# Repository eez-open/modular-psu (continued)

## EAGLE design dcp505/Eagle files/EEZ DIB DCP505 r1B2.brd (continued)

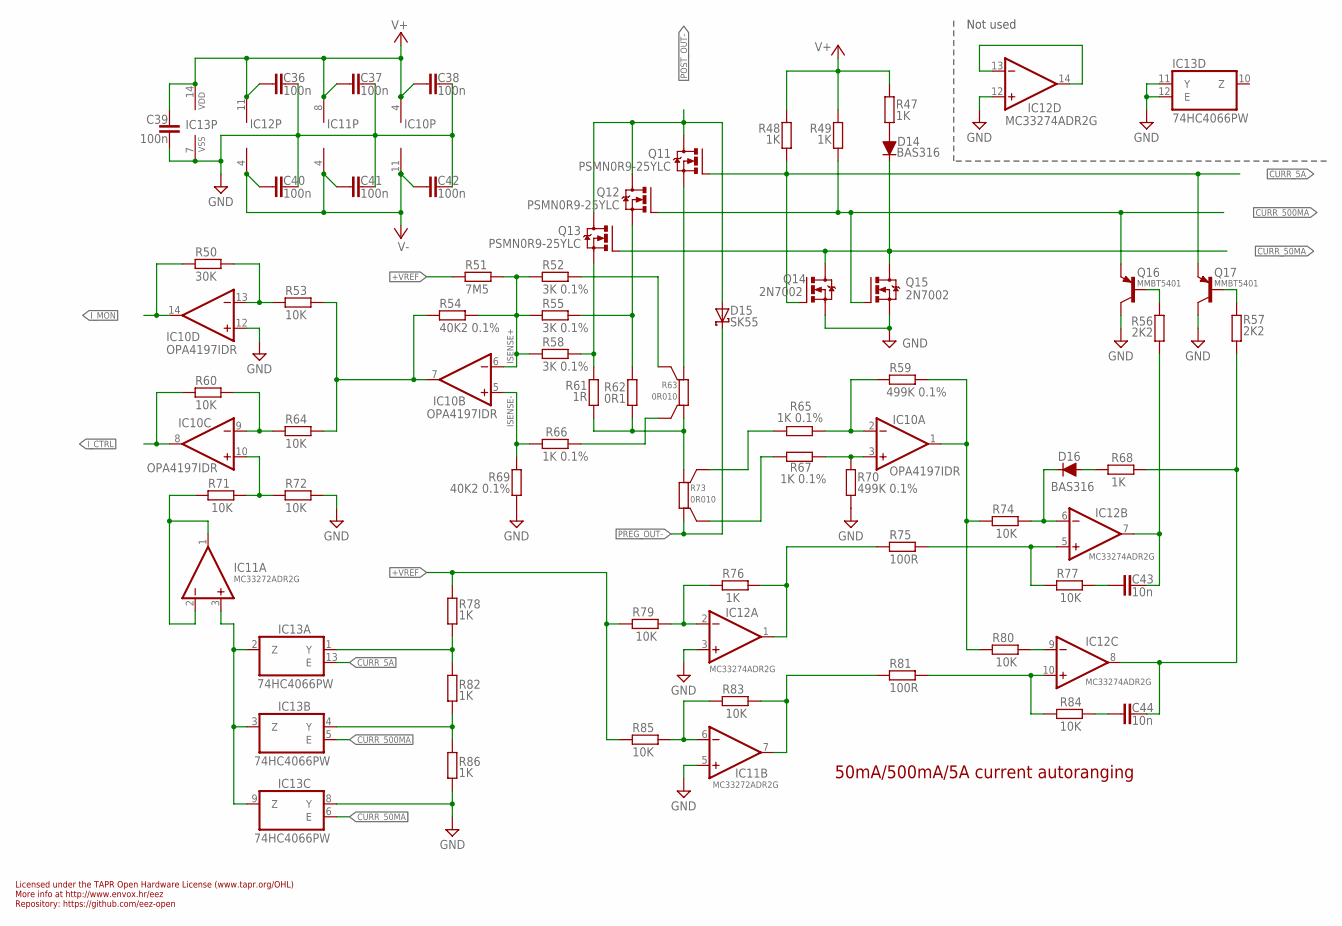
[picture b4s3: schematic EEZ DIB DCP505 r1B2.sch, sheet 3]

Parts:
C36, C37, C38, C39, C40, C41, C42: 100n; C0603
C43, C44: 10n; C0603
D14, D16: BAS316; SOD323-R
D15: SK55; SMB
IC10: OPA4197IDR; SOIC127P600X175-14N
IC11: MC33272ADR2G; SOIC127P600X173-8N
IC12: MC33274ADR2G; SOIC127P600X175-14N
IC13: 74HC4066PW; SOP65P640X120-14N
Q11, Q12, Q13: PSMN0R9-25YLC; SOT669
Q14, Q15: 2N7002; SOT103P240X110-3N; MPN 2N7002-7-F
Q16, Q17: MMBT5401; SOT23-BEC
R47, R48, R49, R68, R76, R78, R82, R86: 1K; R0805
R50: 30K; R0805
R51: 7M5; R0805
R52, R55, R58: 3K 0.1%; R0603
R53, R60, R64, R71, R72, R74, R77, R79, R80, R83, R84, R85: 10K; R0805
R54, R69: 40K2 0.1%; R0603
R56, R57: 2K2; R0805
R59, R70: 499K 0.1%; R0603
R61: 1R; R0805
R62: 0R1; R1206
R63, R73: 0R010; R_H2728
R65, R66, R67: 1K 0.1%; R0603
R75, R81: 100R; R0805

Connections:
+VREF: R51.1, R78.2, R79.2, R85.2; also elsewhere on the board
CURR_5A: IC13.13 (E), Q11.4 (G), Q14.1 (G), Q17.E, R48.2; also elsewhere on the board
CURR_50MA: D14.C, IC13.6 (E), Q13.4 (G), Q14.3 (D), Q15.3 (D); also elsewhere on the board
CURR_500MA: IC13.5 (E), Q12.4 (G), Q15.1 (G), Q16.E, R49.2; also elsewhere on the board
GND: C36.2, C37.2, C38.2, C39.1, C40.2, C41.2, C42.2, IC10.12 (+IN), IC11.5 (+IN), IC12.3 (+IN), IC12.12 (+IN), IC13.7 (VSS), IC13.8 (Y), IC13.11 (Y), IC13.12 (E), Q14.2 (S), Q15.2 (S), Q16.C, Q17.C, R69.1, R70.2, R72.1, R86.1; also elsewhere on the board
ISENSE+: IC10.6 (-IN), R51.2, R52.2, R54.1, R55.2, R58.2
ISENSE-: IC10.5 (+IN), R66.2, R69.2
I_CTRL: IC10.8 (OUT), R60.2; also elsewhere on the board
I_MON: IC10.14 (OUT), R50.2; also elsewhere on the board
unnamed: R65.2, R73.2S
unnamed: R61.2, R62.1, R63.1, R73.2
unnamed: IC11.1 (OUT), IC11.2 (-IN), R71.2
unnamed: IC11.6 (-IN), R83.2, R85.1
unnamed: IC10.2 (-IN), R59.2, R65.1
unnamed: Q11.1 (S), Q11.2 (S), Q11.3 (S), R63.2
unnamed: D14.A, R47.2
unnamed: IC10.1 (OUT), R59.1, R74.2, R80.2
unnamed: IC11.3 (+IN), IC13.2 (Z), IC13.3 (Z), IC13.9 (Z)
unnamed: C43.2, IC12.7 (OUT), R56.2
unnamed: Q16.B, R56.1
unnamed: Q17.B, R57.1
unnamed: IC10.7 (OUT), R53.1, R54.2, R64.1
unnamed: IC10.9 (-IN), R60.1, R64.2
unnamed: IC13.1 (Y), R78.1, R82.2
unnamed: C44.2, IC12.8 (OUT), R57.2, R68.2
unnamed: IC10.10 (+IN), R71.1, R72.2
unnamed: IC13.4 (Y), R82.1, R86.2
unnamed: IC11.7 (OUT), R81.2, R83.1
unnamed: IC10.13 (-IN), R50.1, R53.2
unnamed: R67.2, R73.1S
unnamed: R63.1S, R66.1
unnamed: IC12.2 (-IN), R76.2, R79.1
unnamed: IC12.1 (OUT), R75.2, R76.1
unnamed: IC10.3 (+IN), R67.1, R70.1
unnamed: IC12.13 (-IN), IC12.14 (OUT)
unnamed: Q12.1 (S), Q12.2 (S), Q12.3 (S), R55.1, R62.2
unnamed: D16.C, IC12.6 (-IN), R74.1
unnamed: IC12.5 (+IN), R75.1, R77.2
unnamed: R52.1, R63.2S
unnamed: IC12.9 (-IN), R80.1
unnamed: IC12.10 (+IN), R81.1, R84.2
unnamed: Q13.1 (S), Q13.2 (S), Q13.3 (S), R58.1, R61.1
unnamed: C43.1, R77.1
unnamed: C44.1, R84.1
unnamed: D16.A, R68.1
POST_OUT-: D15.A, Q11.MB (D), Q12.MB (D), Q13.MB (D); also elsewhere on the board
PREG_OUT-: D15.C, R73.1; also elsewhere on the board
V+: C36.1, C37.1, C38.1, C39.2, IC10.4 (V+), IC11.8 (V+), IC12.11 (V-), IC13.14 (VDD), R47.1, R48.1, R49.1; also elsewhere on the board
V-: C40.1, C41.1, C42.1, IC10.11 (V-), IC11.4 (V-), IC12.4 (V+); also elsewhere on the board

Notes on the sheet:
Licensed under the TAPR Open Hardware License (www.tapr.org/OHL)
Repository: https://github.com/eez-open
More info at http://www.envox.hr/eez
50mA/500mA/5A current autoranging
Not used

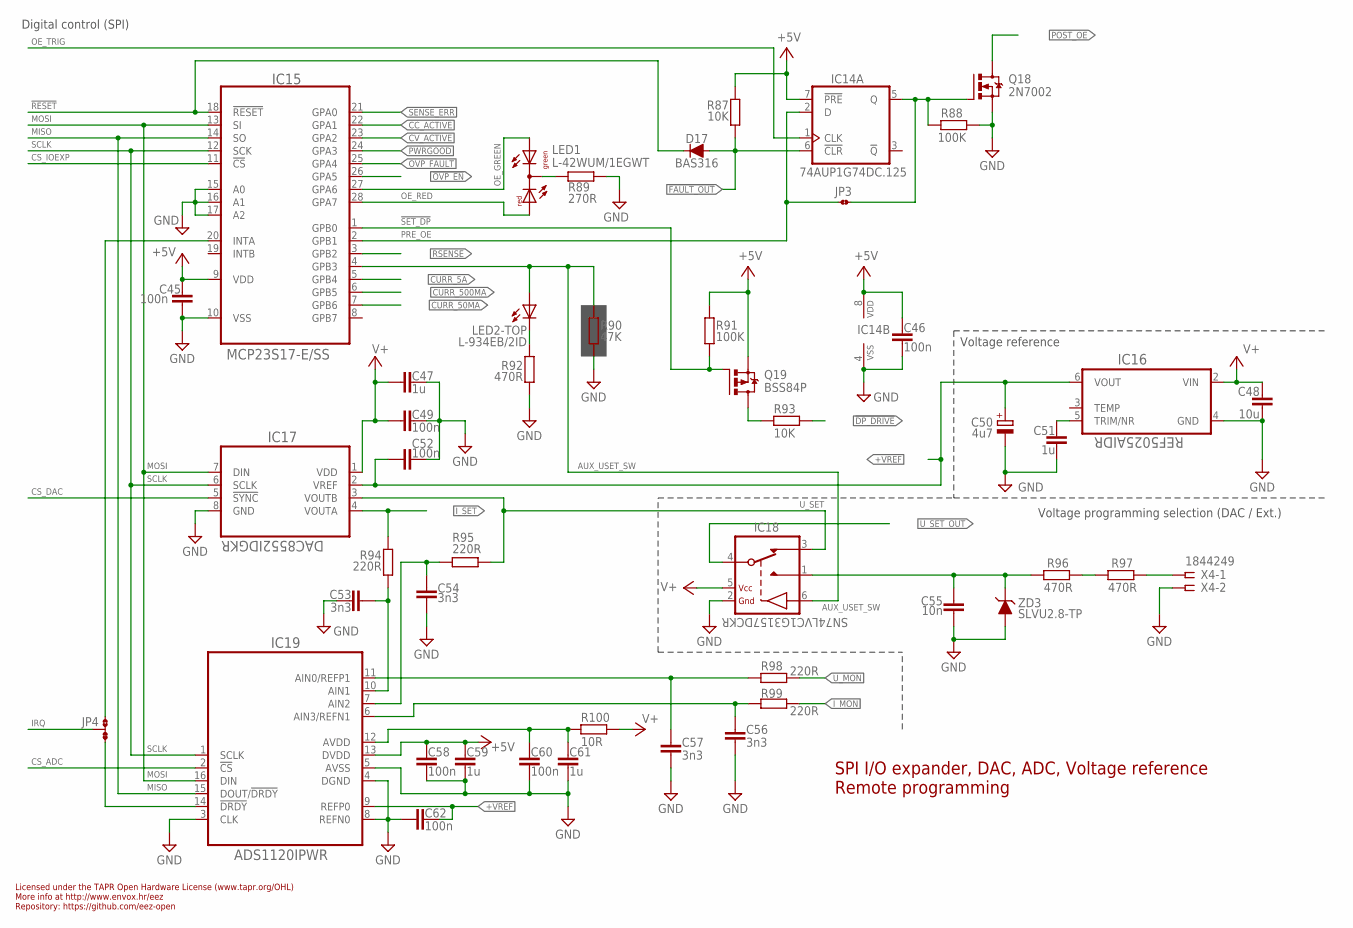
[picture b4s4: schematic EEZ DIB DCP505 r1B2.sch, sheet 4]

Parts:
C45, C46, C49, C52, C58, C60, C62: 100n; C0603
C47, C51, C59, C61: 1u; C0805
C48: 10u; C1206
C50: 4u7; EC1206
C53, C54, C56, C57: 3n3; C0805
C55: 10n; C0805
D17: BAS316; SOD323-R
IC14: 74AUP1G74DC.125; DCU8
IC15: MCP23S17-E/SS; SOP65P780X200-28N
IC16: REF5025AIDR; SOIC127P600X175-8N
IC17: DAC8552IDGKR; DGK8-M
IC18: SN74LVC1G3157DCKR; SOT65P210X110-6N
IC19: ADS1120IPWR; PW(R-PDSO-G16)
JP3: JP2-CUT
JP4: JP3-CUT
LED1: L-42WUM/1EGWT; L-42WUM-1EGWT
LED2: L-934EB/2ID; L-934EB
Q18: 2N7002; SOT103P240X110-3N; MPN 2N7002-7-F
Q19: BSS84P; SOT95P237X112-3N
R87, R93: 10K; R0805
R88, R91: 100K; R0805
R89: 270R; R0805
R90: 47K; R0805
R92, R96, R97: 470R; R0805
R94, R95, R98, R99: 220R; R0805
R100: 10R; R0805
X4: 1844249; MC1,5/5-G-3,5
ZD3: SLVU2.8-TP; SOT23

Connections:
!DP_DRIVE: R93.1; also elsewhere on the board
!DRDY: IC19.14 (!DRDY), JP4.NC
!FAULT_OUT: D17.A, IC14.6 (!CLR), R87.2; also elsewhere on the board
!OVP_EN: IC15.26 (GPA5); also elsewhere on the board
!RESET: D17.C, IC15.18 (!RESET); also elsewhere on the board
!SET_DP: IC15.1 (GPB0), Q19.1 (G), R91.2
+5V: C45.1, C46.2, C58.2, C59.2, IC14.7 (!PRE), IC14.8 (VDD), IC15.9 (VDD), IC19.13 (DVDD), Q19.2 (S), R87.1, R91.1; also elsewhere on the board
+VREF: C50.+, C52.2, C62.2, IC16.6 (VOUT), IC17.2 (VREF), IC19.9 (REFP0); also elsewhere on the board
AUX_IN: C55.2, IC18.1 (NO), R96.1, ZD3.3 (C)
AUX_USET_SW: IC15.4 (GPB3), IC18.6 (CTRL), LED2.TA (A), R90.2
CC_ACTIVE: IC15.22 (GPA1); also elsewhere on the board
CS_ADC: IC19.2 (!CS); also elsewhere on the board
CS_DAC: IC17.5 (!SYNC); also elsewhere on the board
CS_IOEXP: IC15.11 (!CS); also elsewhere on the board
CURR_5A: IC15.5 (GPB4); also elsewhere on the board
CURR_50MA: IC15.7 (GPB6); also elsewhere on the board
CURR_500MA: IC15.6 (GPB5); also elsewhere on the board
CV_ACTIVE: IC15.23 (GPA2); also elsewhere on the board
DP_LED: Q19.3 (D), R93.2
GND: C45.2, C46.1, C47.2, C48.2, C49.1, C50.-, C51.2, C52.1, C53.1, C54.1, C55.1, C56.2, C57.1, C58.1, C59.1, C60.1, C61.1, C62.1, IC14.4 (VSS), IC15.10 (VSS), IC15.15 (A0), IC15.16 (A1), IC15.17 (A2), IC16.4 (GND), IC17.8 (GND), IC18.2 (GND), IC19.3 (CLK), IC19.4 (DGND), IC19.5 (AVSS), IC19.8 (REFN0), Q18.2 (S), R88.1, R89.2, R90.1, R92.1, X4.2, ZD3.1 (A), ZD3.2 (A); also elsewhere on the board
IRQ: JP4.COM; also elsewhere on the board
I_MON: R99.1; also elsewhere on the board
I_SET: IC17.4 (VOUTA), R94.1; also elsewhere on the board
MISO: IC15.14 (SO), IC19.15 (DOUT/!DRDY); also elsewhere on the board
MOSI: IC15.13 (SI), IC17.7 (DIN), IC19.16 (DIN); also elsewhere on the board
unnamed: IC15.20 (INTA), JP4.NO
unnamed: LED1.CC (C), R89.1
unnamed: R96.2, R97.1
unnamed: R97.2, X4.1
unnamed: IC14.5 (Q), JP3.2, Q18.1 (G), R88.2
unnamed: C60.2, C61.2, IC19.12 (AVDD), R100.2
unnamed: C51.1, IC16.5 (TRIM/NR)
unnamed: C53.2, IC19.10 (AIN1), R94.2
unnamed: C57.2, IC19.11 (AIN0/REFP1), R98.2
unnamed: C54.2, IC19.7 (AIN2), R95.2
unnamed: C56.1, IC19.6 (AIN3/REFN1), R99.2
unnamed: LED2.TC (C), R92.2
OE_GREEN: IC15.27 (GPA6), LED1.GREEN (AG)
OE_RED: IC15.28 (GPA7), LED1.RED (AR)
OE_TRIG: IC14.1 (CLK); also elsewhere on the board
OVP_FAULT: IC15.25 (GPA4); also elsewhere on the board
POST_OE: Q18.3 (D); also elsewhere on the board
PRE_OE: IC14.2 (D), IC15.2 (GPB1), JP3.1
PWRGOOD: IC15.24 (GPA3); also elsewhere on the board
RSENSE: IC15.3 (GPB2); also elsewhere on the board
SCLK: IC15.12 (SCK), IC17.6 (SCLK), IC19.1 (SCLK); also elsewhere on the board
SENSE_ERR: IC15.21 (GPA0); also elsewhere on the board
U_MON: R98.1; also elsewhere on the board
U_SET: IC17.3 (VOUTB), IC18.3 (NC), R95.1; also elsewhere on the board
U_SET_OUT: IC18.4 (COM); also elsewhere on the board
V+: C47.1, C48.1, C49.2, IC16.2 (VIN), IC17.1 (VDD), IC18.5 (VDD), R100.1; also elsewhere on the board

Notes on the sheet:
SPI I/O expander, DAC, ADC, Voltage reference
Digital control (SPI)
Voltage reference
Licensed under the TAPR Open Hardware License (www.tapr.org/OHL)
Repository: https://github.com/eez-open
More info at http://www.envox.hr/eez
Remote programming
Voltage programming selection (DAC / Ext.)

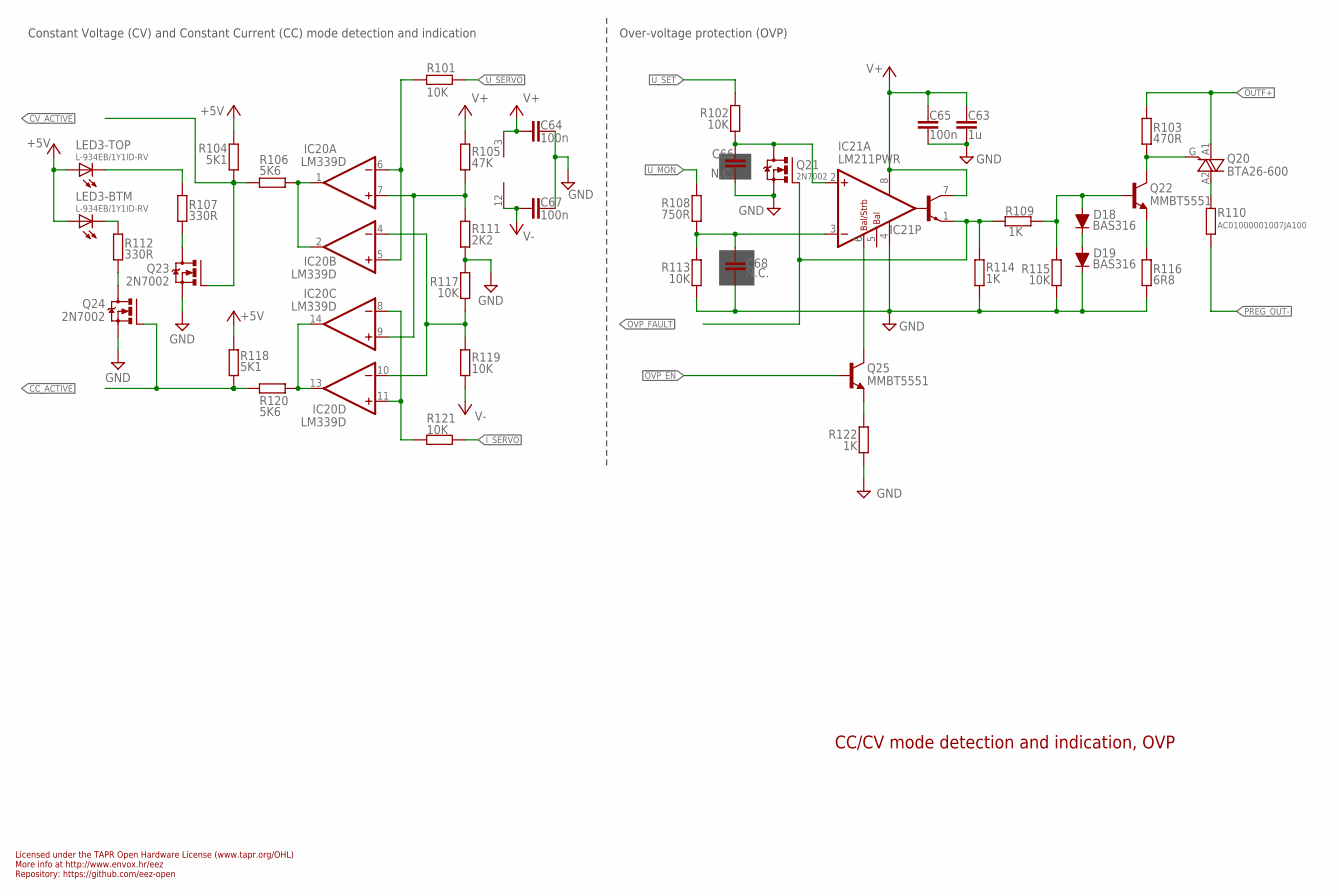
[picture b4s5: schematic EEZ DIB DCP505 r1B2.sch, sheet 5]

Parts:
C63: 1u; C0805
C64, C65, C67: 100n; C0603
C66, C68: N.C.; C0805
D18, D19: BAS316; SOD323-R
IC20: LM339D; SOIC127P600X175-14N
IC21: LM211PWR; PW8_TSSOP8
LED3: L-934EB/1Y1ID-RV; L-934EB
Q20: BTA26-600; TOP3_TRIAC_NOHOLE
Q21: 2N7002; SOT103P240X110-3N; MPN 2N7002-7-F
Q22, Q25: MMBT5551; SOT23-BEC
Q23, Q24: 2N7002; SOT103P240X110-3N
R101, R102, R113, R115, R117, R119, R121: 10K; R0805
R103: 470R; R0805
R104, R118: 5K1; R0805
R105: 47K; R0805
R106, R120: 5K6; R0805
R107, R112: 330R; R0805
R108: 750R; R0805
R109, R114, R122: 1K; R0805
R110: AC01000001007JA100; 0411/15
R111: 2K2; R0805
R116: 6R8; R0805

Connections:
!OVP_EN: Q25.B; also elsewhere on the board
+5V: LED3.BA (A), LED3.TA (A), R104.2, R118.2; also elsewhere on the board
CC_ACTIVE: Q24.1 (G), R118.1, R120.2; also elsewhere on the board
CC_LED: LED3.BC (C), R112.2
CV_ACTIVE: Q23.1 (G), R104.1, R106.2; also elsewhere on the board
CV_LED: LED3.TC (C), R107.1
GND: C63.2, C64.1, C65.1, C66.1, C67.1, C68.1, D19.C, IC21.4 (V-), Q21.2 (S), Q23.2 (S), Q24.2 (S), R111.1, R113.2, R114.2, R115.1, R116.1, R117.2, R122.2; also elsewhere on the board
I_SERVO: R121.1; also elsewhere on the board
unnamed: Q20.A2, R110.2
unnamed: Q20.G, Q22.C, R103.1
unnamed: Q22.E, R116.2
unnamed: D18.C, D19.A
unnamed: D18.A, Q22.B, R109.1, R115.2
unnamed: IC21.6 (BAL/STRB), Q25.C
unnamed: Q25.E, R122.1
unnamed: C66.2, IC21.2 (+IN), Q21.3 (D), R102.2
unnamed: C68.2, IC21.3 (-IN), R108.2, R113.1
unnamed: Q24.3 (D), R112.1
unnamed: IC20.1 (OUT), IC20.2 (OUT), R106.1
unnamed: IC20.13 (OUT), IC20.14 (OUT), R120.1
unnamed: Q23.3 (D), R107.2
unnamed: IC20.5 (+IN), IC20.6 (-IN), R101.2
unnamed: IC20.8 (-IN), IC20.11 (+IN), R121.2
unnamed: IC20.7 (+IN), IC20.9 (+IN), R105.1, R111.2
unnamed: IC20.4 (-IN), IC20.10 (-IN), R117.1, R119.2
OUTF+: Q20.A1, R103.2; also elsewhere on the board
OVP_FAULT: IC21.1 (E), Q21.1 (G), R109.2, R114.1; also elsewhere on the board
PREG_OUT-: R110.1; also elsewhere on the board
U_MON: R108.1; also elsewhere on the board
U_SERVO: R101.1; also elsewhere on the board
U_SET: R102.1; also elsewhere on the board
V+: C63.1, C64.2, C65.2, IC20.3 (V+), IC21.7 (C), IC21.8 (V+), R105.2; also elsewhere on the board
V-: C67.2, IC20.12 (GND), R119.1; also elsewhere on the board

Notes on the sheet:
Licensed under the TAPR Open Hardware License (www.tapr.org/OHL)
Repository: https://github.com/eez-open
More info at http://www.envox.hr/eez
CC/CV mode detection and indication, OVP
Constant Voltage (CV) and Constant Current (CC) mode detection and indication
Over-voltage protection (OVP)

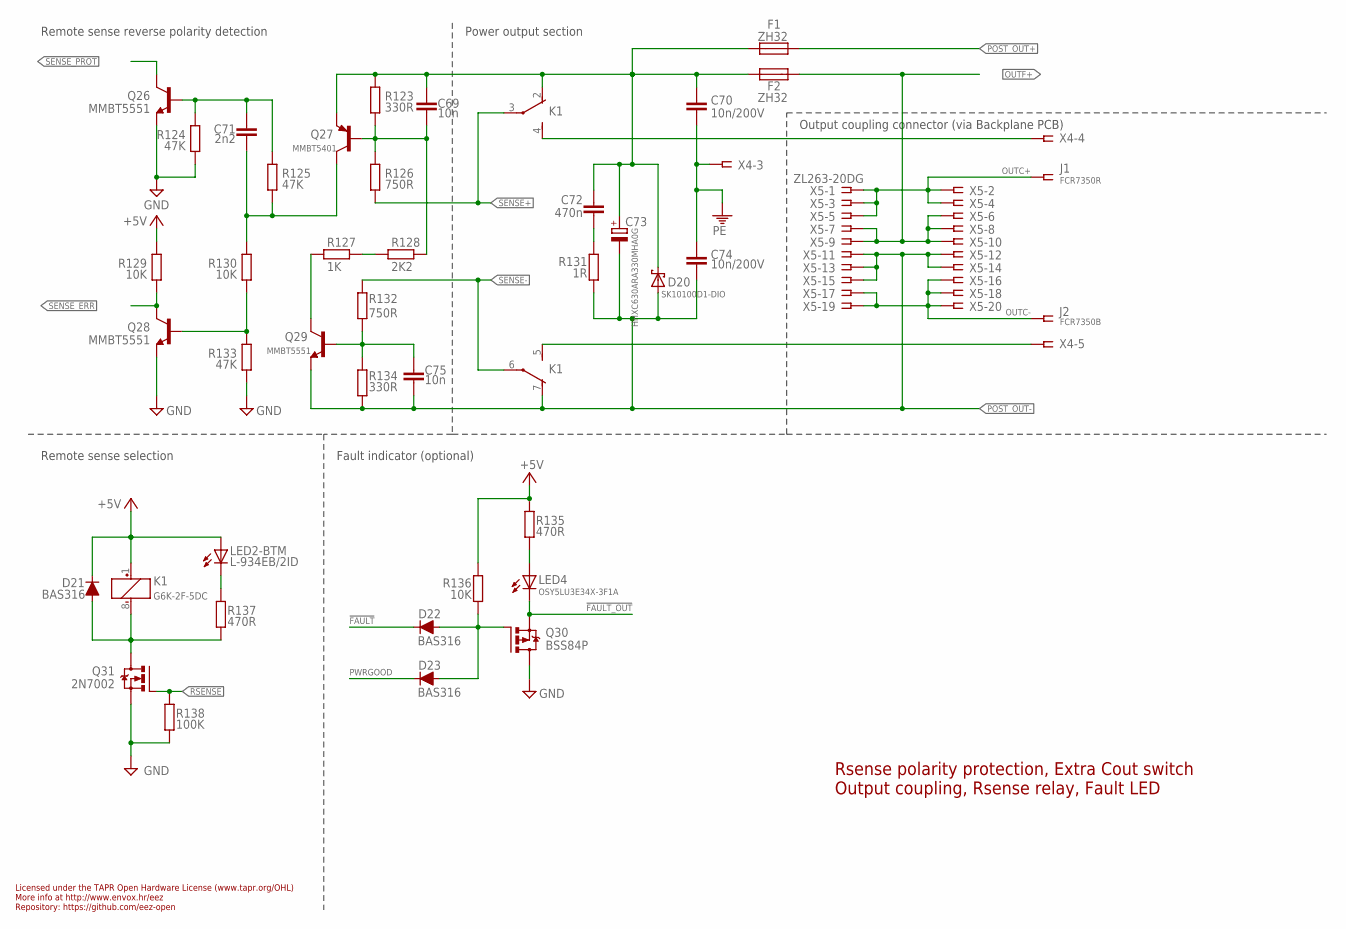
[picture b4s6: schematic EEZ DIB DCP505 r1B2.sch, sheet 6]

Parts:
C69, C75: 10n; C0805
C70, C74: 10n/200V; C1206
C71: 2n2; C0805
C72: 470n; C1206
C73: HHXC630ARA330MHA0G; CAPAE830X1050N
D20: SK10100D1-DIO; TO252-L
D21, D22, D23: BAS316; SOD323-R
F1, F2: ZH32
J1: FCR7350R; S16N-PC
J2: FCR7350B; S16N-PC
K1: G6K-2F-5DC; G6K-2F; MPN G6K-2F DC24
LED2: L-934EB/2ID; L-934EB
LED4: OSY5LU3E34X-3F1A; OSG8
Q26, Q28, Q29: MMBT5551; SOT23-BEC
Q27: MMBT5401; SOT23-BEC
Q30: BSS84P; SOT95P237X112-3N
Q31: 2N7002; SOT103P240X110-3N; MPN 2N7002-7-F
R123, R134: 330R; R0805
R124, R125, R133: 47K; R0805
R126, R132: 750R; R0805
R127: 1K; R0805
R128: 2K2; R0805
R129, R130, R136: 10K; R0805
R131: 1R; R0805
R135, R137: 470R; R0805
R138: 100K; R0805
X4: 1844249; MC1,5/5-G-3,5
X5: ZL263-20DG; SSW-110-02-T-D-RA

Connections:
!FAULT: D22.C; also elsewhere on the board
!FAULT_OUT: LED4.C, Q30.2 (S); also elsewhere on the board
+5V: D21.C, K1.1 (+), LED2.BA (A), R129.2, R135.2, R136.1; also elsewhere on the board
GND: Q26.E, Q28.E, Q30.3 (D), Q31.2 (S), R124.1, R133.1, R138.1; also elsewhere on the board
unnamed: C69.1, C70.1, C72.1, C73.+, D20.3 (C), F1.2, F2.1, K1.2 (O), Q27.E, R123.2
unnamed: D22.A, D23.A, Q30.1 (G), R136.2
unnamed: LED4.A, R135.1
unnamed: C69.2, Q27.B, R123.1, R126.2, R128.2
unnamed: C71.2, Q27.C, R125.1, R130.2
unnamed: Q29.C, R127.1
unnamed: C75.1, Q29.B, R132.1, R134.2
unnamed: C71.1, Q26.B, R124.2, R125.2
unnamed: Q28.B, R130.1, R133.2
unnamed: C72.2, R131.2
unnamed: D21.A, K1.8 (-), Q31.3 (D), R137.1
unnamed: K1.4 (S), X4.4
unnamed: K1.5 (S), X4.5
unnamed: LED2.BC (C), R137.2
unnamed: R127.2, R128.1
OUTC+: J1.1, J1.NC1, J1.NC2, J1.NC3, J1.NC4, X5.1, X5.2, X5.3, X5.4, X5.5
OUTC-: J2.1, J2.NC1, J2.NC2, J2.NC3, J2.NC4, X5.16, X5.17, X5.18, X5.19, X5.20
OUTF+: F2.2, X5.6, X5.7, X5.8, X5.9, X5.10; also elsewhere on the board
PE: C70.2, C74.1, X4.3; also elsewhere on the board
POST_OUT+: F1.1; also elsewhere on the board
POST_OUT-: C73.-, C74.2, C75.2, D20.1 (A), D20.2 (A), K1.7 (O), Q29.E, R131.1, R134.1, X5.11, X5.12, X5.13, X5.14, X5.15; also elsewhere on the board
PWRGOOD: D23.C; also elsewhere on the board
RSENSE: Q31.1 (G), R138.2; also elsewhere on the board
SENSE+: K1.3, R126.1; also elsewhere on the board
SENSE-: K1.6, R132.2; also elsewhere on the board
SENSE_ERR: Q28.C, R129.1; also elsewhere on the board
SENSE_PROT: Q26.C; also elsewhere on the board

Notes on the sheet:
Rsense polarity protection, Extra Cout switch
Licensed under the TAPR Open Hardware License (www.tapr.org/OHL)
Repository: https://github.com/eez-open
More info at http://www.envox.hr/eez
Remote sense reverse polarity detection
Remote sense selection
Output coupling, Rsense relay, Fault LED
Fault indicator (optional)
Output coupling connector (via Backplane PCB)
Power output section

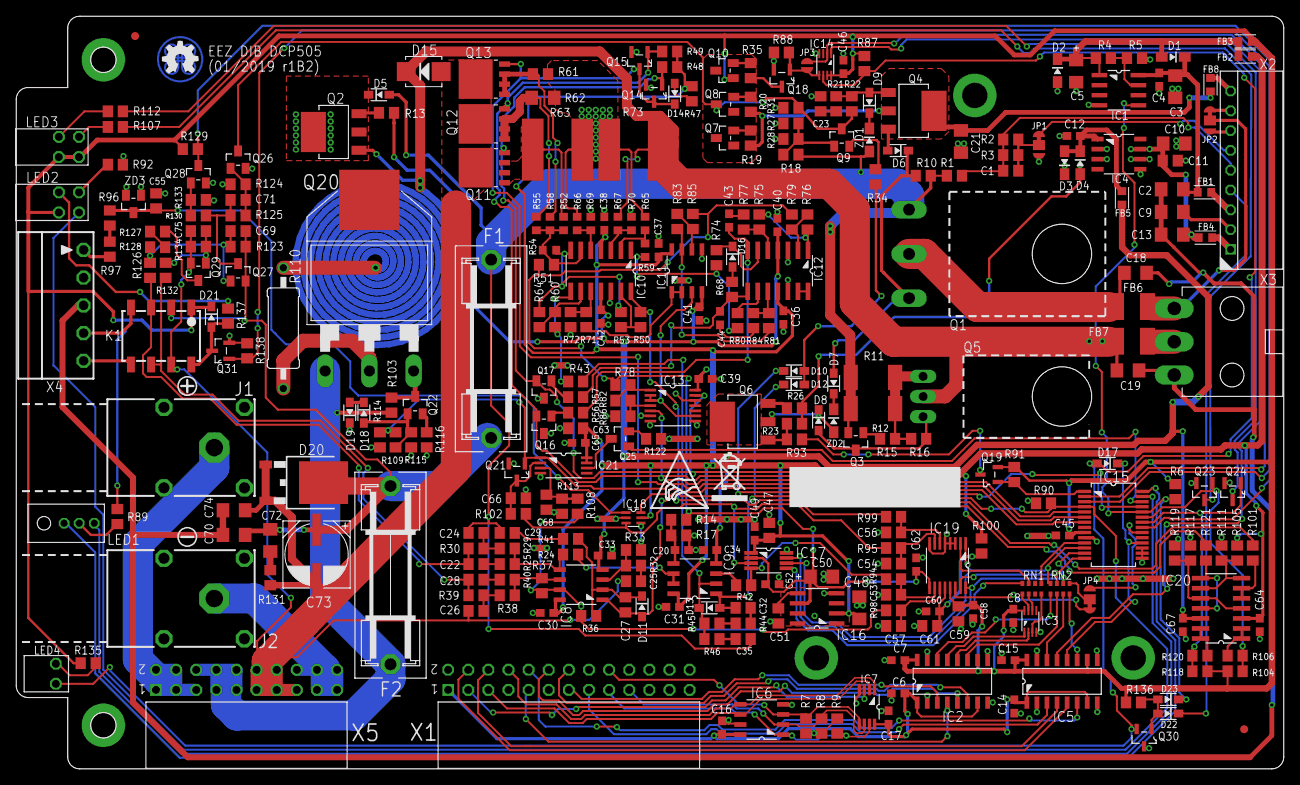
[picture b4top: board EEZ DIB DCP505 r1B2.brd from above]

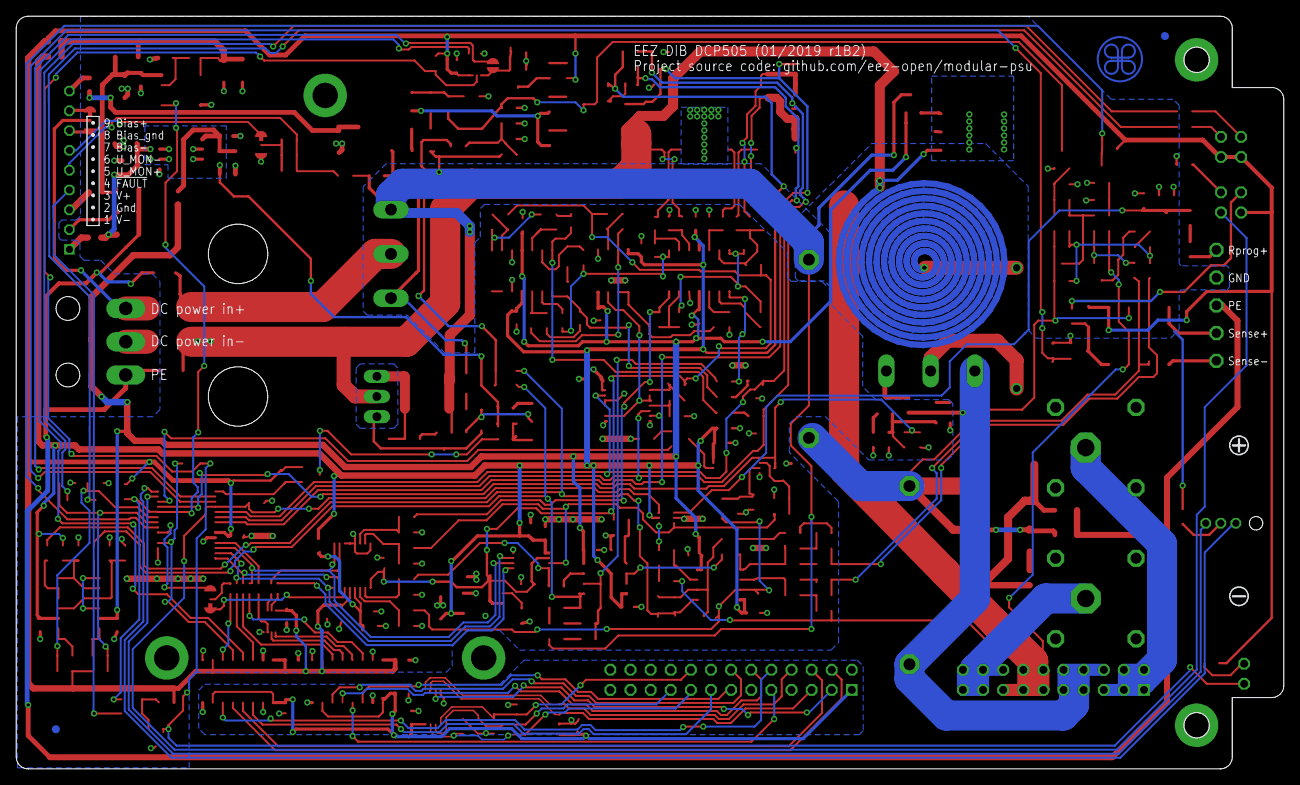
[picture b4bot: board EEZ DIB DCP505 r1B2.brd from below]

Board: 2 copper layers, 160.0 x 95.0 mm, 328 parts (4 on the bottom side), 220 nets.

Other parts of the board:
EEZ_SIGNATURE: SIGNATURESMALL; SIGNATURE_5MM
U$1: RECYCLE_BIN1/8
U$6: ESD_SYMBOL
